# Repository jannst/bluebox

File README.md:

# BlueBox
The Bluebox Project aims to develop a board that incorporates a Bluetooth audio receiver and a power amplifier, designed to upgrade passive speakers into active Bluetooth speakers. The selection of Through-Hole Technology (THT) parts ensures that this project can be easily assembled in workshops without the need for sophisticated tools. The project utilizes the BM83 module from Microchip as the Bluetooth receiver.

## Prototype I (2023)

The first prototype utilized an external audio board with a Texas Instruments TPA3116D amplifier. Unfortunately, a significant amount of digital switching noise from the BM83 module is amplified by the amplifier.

## Prototype II (WIP)
The second prototype will utilize a Texas Instruments TAS5828M amplifier. The amplifier chip will be integrated into the custom PCB. The advantage of the TAS5828M lies in its digital input, which is expected to prevent the amplification of switching noise.

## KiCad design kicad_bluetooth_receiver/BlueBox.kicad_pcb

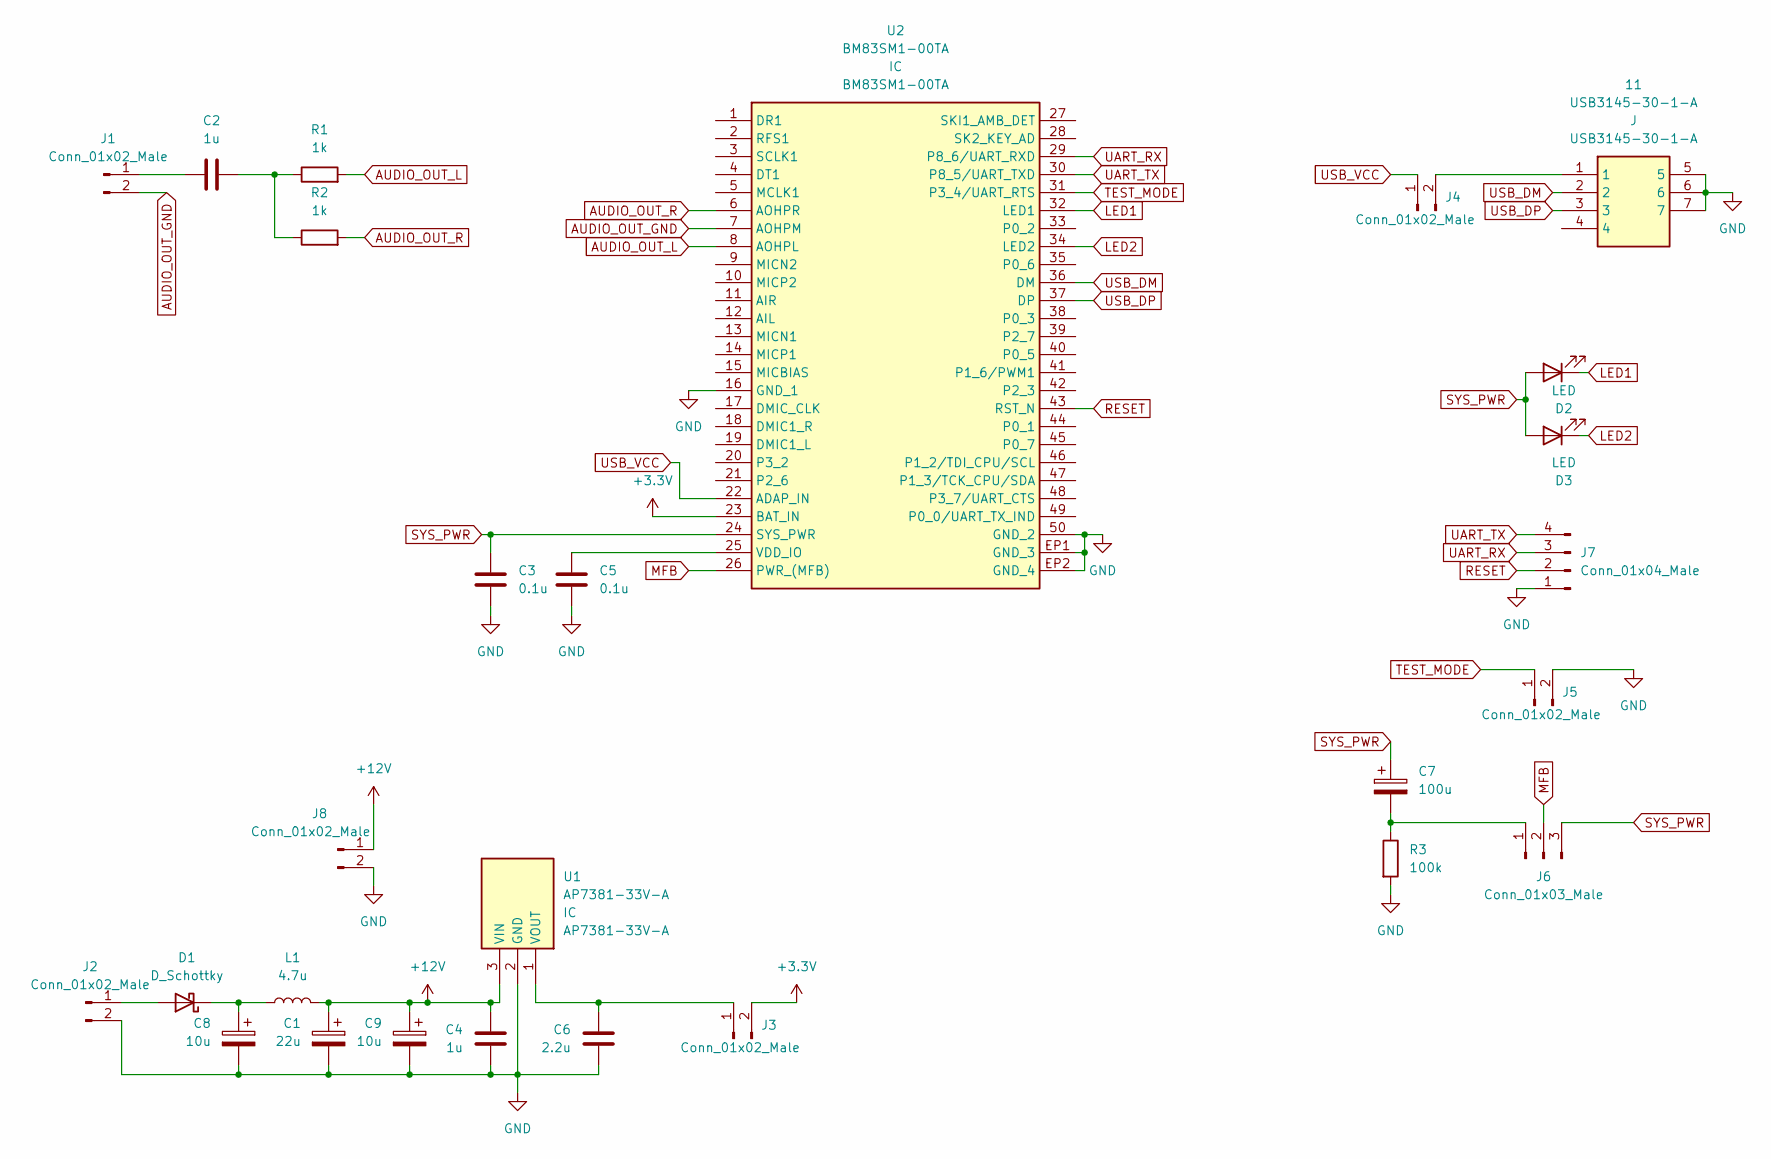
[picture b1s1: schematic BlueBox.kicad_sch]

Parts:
11: USB3145-30-1-A; USB3145301A; Mouser Part Number 640-USB3145-30-1-A
C1: 22u; CP_Radial_D5.0mm_P2.00mm
C2, C4: 1u; C_Disc_D5.0mm_W2.5mm_P5.00mm
C3, C5: 0.1u; C_Disc_D5.0mm_W2.5mm_P5.00mm
C6: 2.2u; C_Disc_D5.0mm_W2.5mm_P5.00mm
C7: 100u; CP_Radial_D7.5mm_P2.50mm
C8, C9: 10u; CP_Radial_D5.0mm_P2.00mm
D1: D_Schottky; D_DO-41_SOD81_P7.62mm_Horizontal
D2, D3: LED; LED_D5.0mm
J1, J2, J3, J4, J5, J8: Conn_01x02_Male; PinHeader_1x02_P2.54mm_Vertical
J6: Conn_01x03_Male; PinHeader_1x03_P2.54mm_Vertical
J7: Conn_01x04_Male; PinHeader_1x04_P2.54mm_Vertical
L1: 4.7u; L_Radial_D10.5mm_P5.00mm_Abacron_AISR-01
R1, R2: 1k; R_Axial_DIN0207_L6.3mm_D2.5mm_P7.62mm_Horizontal
R3: 100k; R_Axial_DIN0207_L6.3mm_D2.5mm_P7.62mm_Horizontal
U1: AP7381-33V-A; AP738133VA; Mouser Part Number 621-AP7381-33V-A
U2: BM83SM1-00TA; BM83SM100TA; Mouser Part Number 579-BM83SM1-00TA

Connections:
+3.3V: J3.2, U2.23 (BAT_IN)
+12V: C1.1, C4.2, C9.1, J8.1, L1.2, U1.3 (VIN)
AUDIO_OUT_GND: J1.2, U2.7 (AOHPM)
AUDIO_OUT_L: R1.2, U2.8 (AOHPL)
AUDIO_OUT_R: R2.2, U2.6 (AOHPR)
GND: 11.5, 11.6, 11.7, C1.2, C3.2, C4.1, C5.2, C6.1, C8.2, C9.2, J2.2, J5.2, J7.1, J8.2, R3.2, U1.2 (GND), U2.16 (GND_1), U2.50 (GND_2), U2.EP1 (GND_3), U2.EP2 (GND_4)
LED1: D2.1 (K), U2.32 (LED1)
LED2: D3.1 (K), U2.34 (LED2)
MFB: J6.2, U2.26 (PWR_(MFB))
unnamed: C5.1, U2.25 (VDD_IO)
unnamed: C6.2, J3.1, U1.1 (VOUT)
unnamed: C7.2, J6.1, R3.1
unnamed: C8.1, D1.1 (K), L1.1
unnamed: D1.2 (A), J2.1
unnamed: C2.2, J1.1
unnamed: 11.1, J4.2
unnamed: C2.1, R1.1, R2.1
RESET: J7.2, U2.43 (RST_N)
SYS_PWR: C3.1, C7.1, D2.2 (A), D3.2 (A), J6.3, U2.24 (SYS_PWR)
TEST_MODE: J5.1, U2.31 (P3_4/UART_RTS)
UART_RX: J7.3, U2.29 (P8_6/UART_RXD)
UART_TX: J7.4, U2.30 (P8_5/UART_TXD)
USB_DM: 11.2, U2.36 (DM)
USB_DP: 11.3, U2.37 (DP)
USB_VCC: J4.1, U2.22 (ADAP_IN)

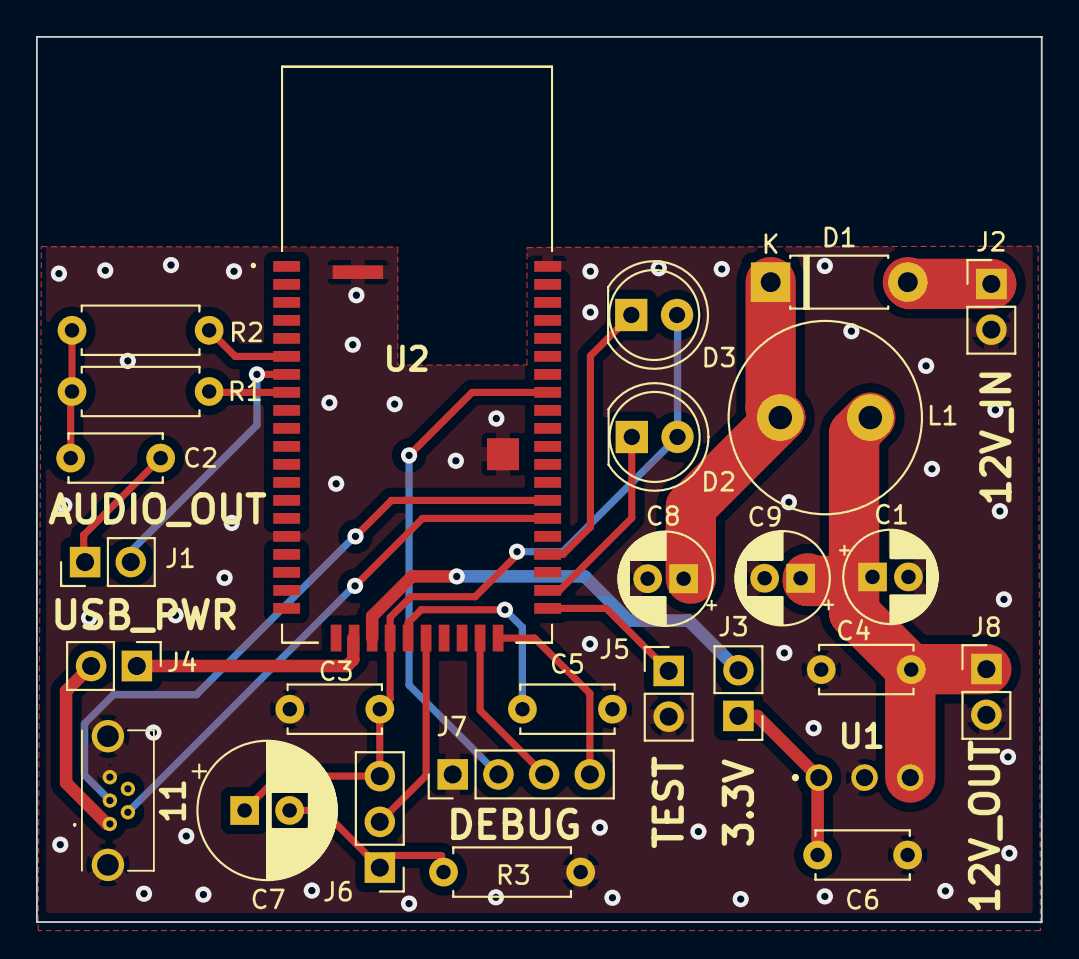
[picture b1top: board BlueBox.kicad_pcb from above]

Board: 2 copper layers, 55.8 x 49.2 mm, 27 parts (0 on the bottom side), 25 nets.
